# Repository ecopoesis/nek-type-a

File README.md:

# Natural Ergonomic Keyboard, Type A

One of the best keyboards ever made is the [Microsoft Natural Keyboard](https://en.wikipedia.org/wiki/Microsoft_Natural_Keyboard). 
Unfortunately modern versions of the natural keyboard are significantly worse then the original mid 90s versions. 
The goal of this project is to create a high-quality, open-source replacement for the natural keyboard.

## Goals

* Standard split-QWERTY layout mirroring the Microsoft Natural Keyboards
* No built-in number pad
* High quality mechanical switches
* Bluetooth or USB connection
* Plug and play (no-solder) microcontroller replacement
* Heirloom quality

## Design

The keyboard (and repo) is divided into the following parts:

* Body
* Electronics

### Body

The body has three major components: the aluminum unibody, the left and right steel switch plates and the acrylic access panel. 

Source files:
* `*.kbd.json` files are generated using the [keyboard_layout_editor.com](http://www.keyboard-layout-editor.com)
* `*.svg` and `*.dxf` files are built using [swillkb's Plate and Case Builder](http://builder.swillkb.com/) based on the `.kbd.json` files
  * The `*switch.*` files are the laser cutter templates
* `body.stl` and `body.step` are built from the [CadQuery](https://github.com/dcowden/cadquery) source file `body.py`. The easiest way to build this is to use the provided Docker image and `Makefile`:
  ```bash
    cd body && make
  ```    

You will need to have the following manufactured:
* Case
  * [`body.step`](body/target/body.step)
  * [screw tapping plan](drawings/bottom_view.pdf)
  * CNC from aluminum at [Xometry](http://xometry.com)
* Rubber gaskets
  * [`left_closed.dxf`](body/build_data/left_closed.dxf)
  * [`right_closed.dxf`](body/build_data/right_closed.dxf)
  * Laser cut from Buna-N Rubber 0.031 in at [Big Blue Saw](https://www.bigbluesaw.com/)
* Acrylic plate
  * [`plate.dxf`](drawings/plate.dxf)
  * Laser cut from Acrylic Plastic, Clear 0.118 in at [Big Blue Saw](https://www.bigbluesaw.com/)
* Steel plates
  * [`left_switch.dxf`](body/build_data/left_switch.dxf)
  * [`right_switch.dxf`](body/build_data/right_switch.dxf)
  * Laser cut from 304 Stainless Steel 1.5mm at [Lasergist](https://www.lasergist.com/)
  
You will need to buy:
* 8x M5x8mm screws
* 4x M5x20mm screws
* 3x M3 standoffs
* 3x M3x5mm screws
* 4x [M5 feet](https://www.amazon.com/gp/product/B000PWU9CC)
* 1x [USB-C panel mount](https://www.datapro.net/products/usb-c-panel-mount-extension-cable.html)
* 1x [19mm latching button](https://www.amazon.com/gp/product/B06XQZ3Y76)
* 1x [2-pin JST-XHP connector](https://www.amazon.com/gp/product/B0774TF39N)

### Electronics

The electronics are designed to be swappable. The left and right PCBs only contain the keyboard matrices and the ribbon connectors to the center PCB.

The PCBs can be made directly from the `BRD` files by [OSH Park](http://oshpark.com).

#### Left
[`left.brd`](eagle/nek-type-a/left.brd)

#### Right
[`right.brd`](eagle/nek-type-a/right.brd)

#### Center
[`center.brd`](eagle/nek-type-a/center.brd)

The center PCB uses a [MCP23017E-S/P](https://www.microchip.com/wwwproducts/en/MCP23017) I/O expander hooked to the microprocessor via the I2C bus.
The center is designed to use development boards that conform the [Adafruit](https://www.adafruit.com/feather) interface. 
The Feather is connected via headers on the center PCB so it can be swapped for models with different connectivity in the future was standards evolve.

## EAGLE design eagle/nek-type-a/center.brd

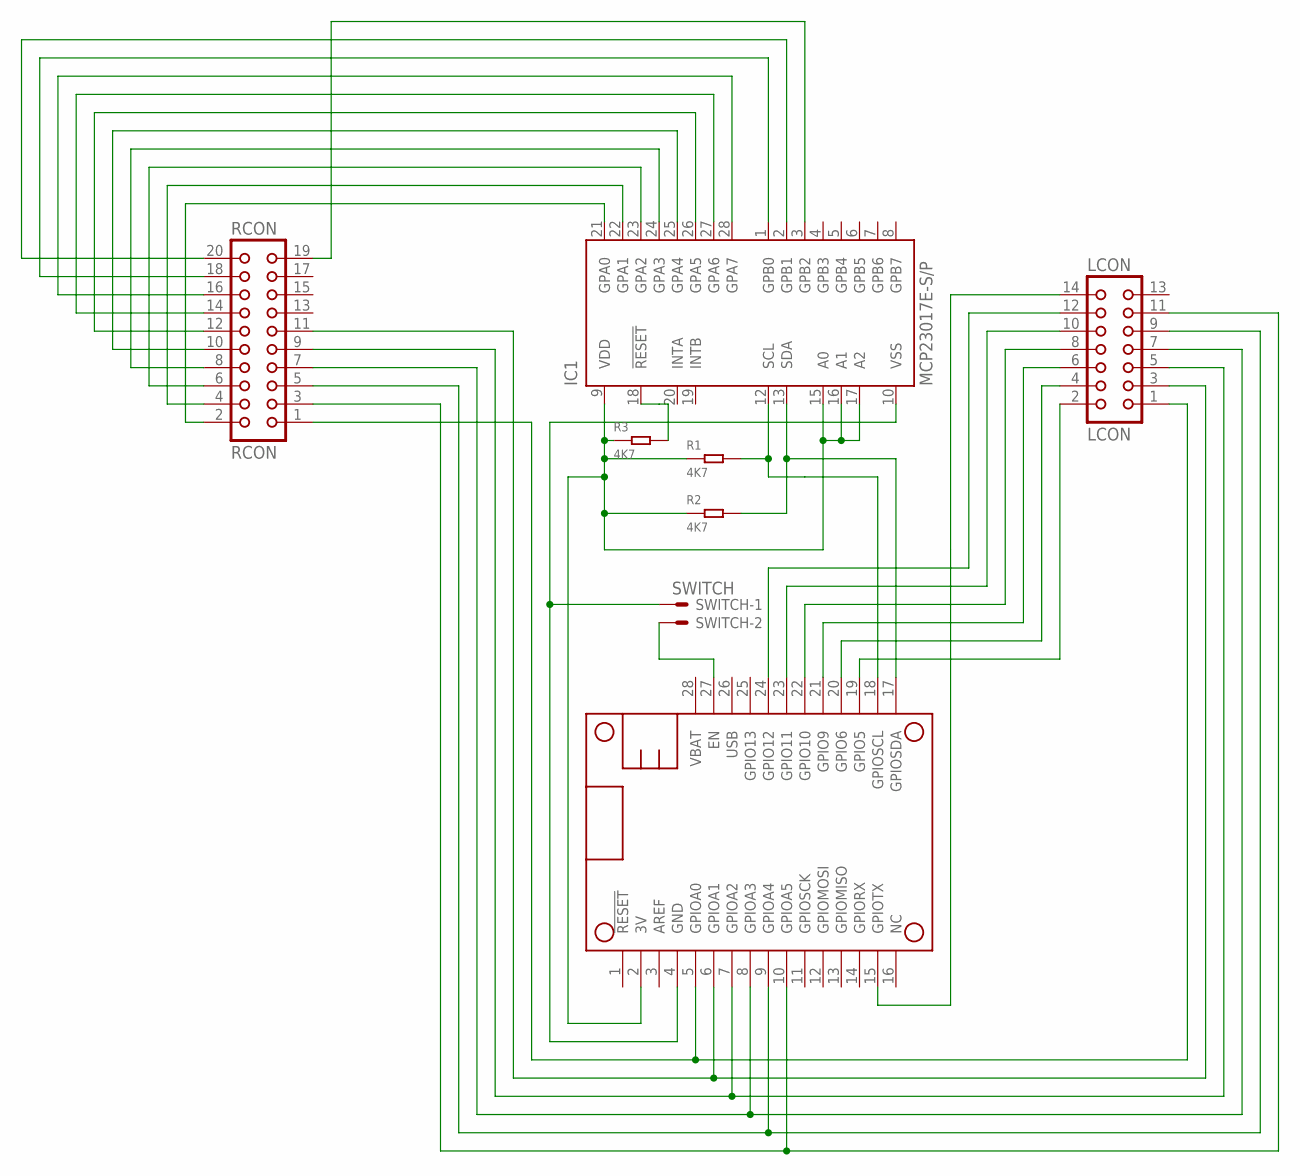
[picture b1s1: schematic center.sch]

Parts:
IC1: MCP23017E-S/P; DIL28-3
LCON: LCON; CON14
MS1: FEATHERWING_NODIM; FEATHERWING_DIM
R1, R2, R3: 4K7; PR-D2.3XL6.5MM
RCON: RCON; CON20
SWITCH: SWITCH; JST-XH-02-PACKAGE-LONG-PAD

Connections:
3V: IC1.9 (VDD), IC1.15 (A0), IC1.16 (A1), IC1.17 (A2), MS1.2 (3V), R1.1, R2.1, R3.1
EN: MS1.27 (EN), SWITCH.2
GND: IC1.10 (VSS), MS1.4 (GND), SWITCH.1
LCOL1: LCON.2, MS1.19 (GPIO5)
LCOL2: LCON.4, MS1.20 (GPIO6)
LCOL3: LCON.6, MS1.21 (GPIO9)
LCOL4: LCON.8, MS1.22 (GPIO10)
LCOL5: LCON.10, MS1.23 (GPIO11)
LCOL6: LCON.12, MS1.24 (GPIO12)
LCOL7: LCON.14, MS1.15 (GPIOTX)
RCOL1: IC1.21 (GPA0), RCON.2
RCOL2: IC1.22 (GPA1), RCON.4
RCOL3: IC1.23 (GPA2), RCON.6
RCOL4: IC1.24 (GPA3), RCON.8
RCOL5: IC1.25 (GPA4), RCON.10
RCOL6: IC1.26 (GPA5), RCON.12
RCOL7: IC1.27 (GPA6), RCON.14
RCOL8: IC1.28 (GPA7), RCON.16
RCOL9: IC1.1 (GPB0), RCON.18
RCOL10: IC1.2 (GPB1), RCON.20
RCOL11: IC1.3 (GPB2), RCON.19
RESET: IC1.18 (!RESET), R3.2
ROW1: LCON.1, MS1.5 (GPIOA0), RCON.1
ROW2: LCON.3, MS1.6 (GPIOA1), RCON.11
ROW3: LCON.5, MS1.7 (GPIOA2), RCON.9
ROW4: LCON.7, MS1.8 (GPIOA3), RCON.7
ROW5: LCON.9, MS1.9 (GPIOA4), RCON.5
ROW6: LCON.11, MS1.10 (GPIOA5), RCON.3
SCL: IC1.12 (SCL), MS1.18 (GPIOSCL), R1.2
SDA: IC1.13 (SDA), MS1.17 (GPIOSDA), R2.2

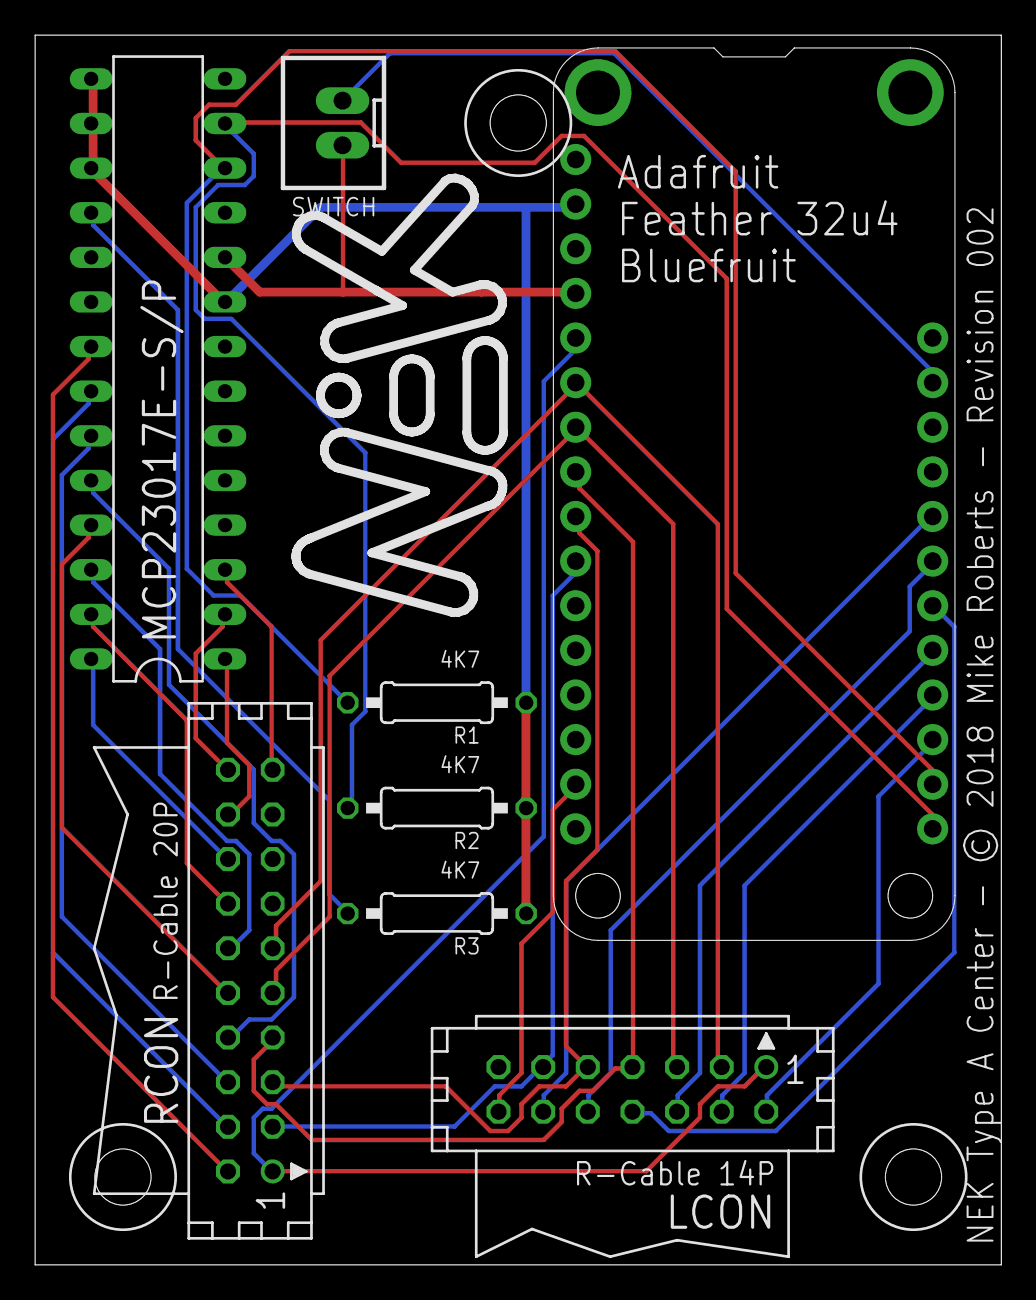
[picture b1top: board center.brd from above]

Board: 2 copper layers, 55.0 x 70.0 mm, 8 parts (0 on the bottom side), 30 nets.

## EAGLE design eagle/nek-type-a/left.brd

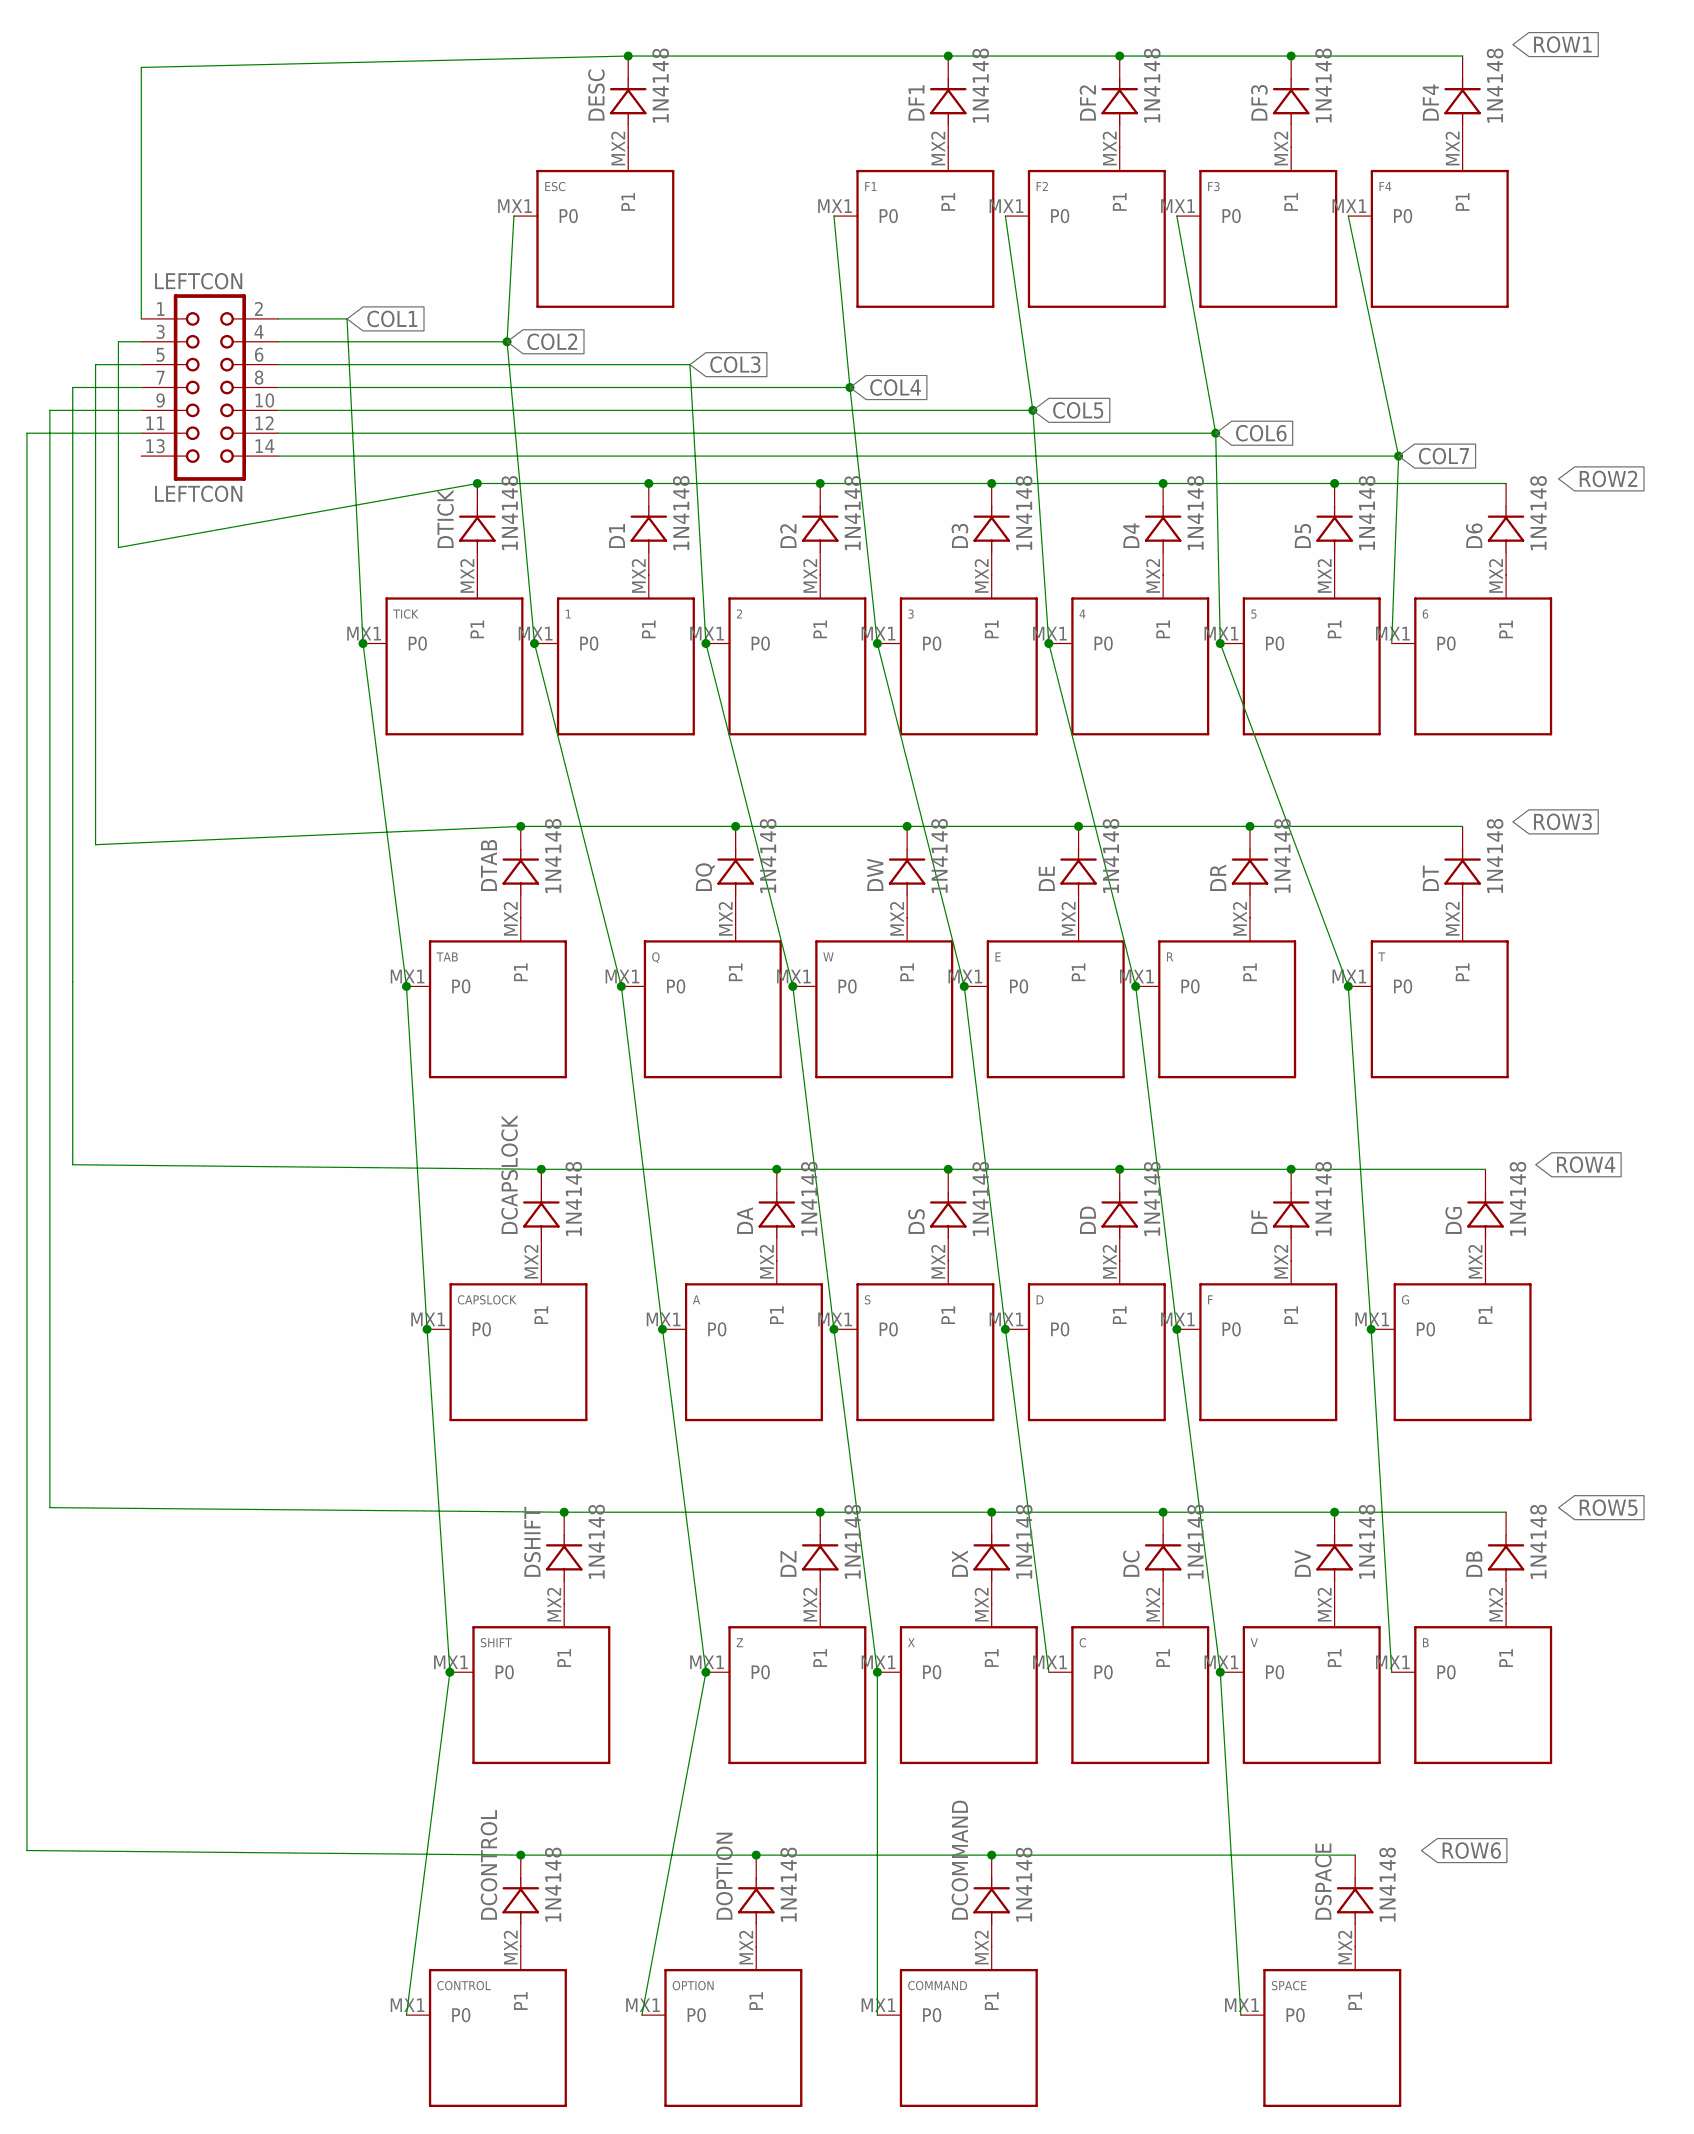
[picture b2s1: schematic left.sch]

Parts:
1, 2, 3, 4, 5, 6: KEYSWITCH-PLAIN-MX-1U; MX-1U
A: KEYSWITCH-PLAIN-MX-1U; MX-1U
B: KEYSWITCH-PLAIN-MX-1U; MX-1U
C: KEYSWITCH-PLAIN-MX-1U; MX-1U
CAPSLOCK: KEYSWITCH-PLAIN-MX-1U; MX-1U
COMMAND: KEYSWITCH-PLAIN-MX-1U; MX-1U
CONTROL: KEYSWITCH-PLAIN-MX-1U; MX-1U
D: KEYSWITCH-PLAIN-MX-1U; MX-1U
D1, D2, D3, D4, D5, D6: 1N4148; DO-35
DA: 1N4148; DO-35
DB: 1N4148; DO-35
DC: 1N4148; DO-35
DCAPSLOCK: 1N4148; DO-35
DCOMMAND: 1N4148; DO-35
DCONTROL: 1N4148; DO-35
DD: 1N4148; DO-35
DE: 1N4148; DO-35
DESC: 1N4148; DO-35
DF, DF1, DF2, DF3, DF4: 1N4148; DO-35
DG: 1N4148; DO-35
DOPTION: 1N4148; DO-35
DQ: 1N4148; DO-35
DR: 1N4148; DO-35
DS: 1N4148; DO-35
DSHIFT: 1N4148; DO-35
DSPACE: 1N4148; DO-35
DT: 1N4148; DO-35
DTAB: 1N4148; DO-35
DTICK: 1N4148; DO-35
DV: 1N4148; DO-35
DW: 1N4148; DO-35
DX: 1N4148; DO-35
DZ: 1N4148; DO-35
E: KEYSWITCH-PLAIN-MX-1U; MX-1U
ESC: KEYSWITCH-PLAIN-MX-1U; MX-1U
F, F1, F2, F3, F4: KEYSWITCH-PLAIN-MX-1U; MX-1U
G: KEYSWITCH-PLAIN-MX-1U; MX-1U
LEFTCON: LEFTCON; CON14
OPTION: KEYSWITCH-PLAIN-MX-1U; MX-1U
Q: KEYSWITCH-PLAIN-MX-1U; MX-1U
R: KEYSWITCH-PLAIN-MX-1U; MX-1U
S: KEYSWITCH-PLAIN-MX-1U; MX-1U
SHIFT: KEYSWITCH-PLAIN-MX-2U; MX-2U
SPACE: KEYSWITCH-PLAIN-MX-2U; MX-2U
T: KEYSWITCH-PLAIN-MX-1U; MX-1U
TAB: KEYSWITCH-PLAIN-MX-1U; MX-1U
TICK: KEYSWITCH-PLAIN-MX-1U; MX-1U
V: KEYSWITCH-PLAIN-MX-1U; MX-1U
W: KEYSWITCH-PLAIN-MX-1U; MX-1U
X: KEYSWITCH-PLAIN-MX-1U; MX-1U
Z: KEYSWITCH-PLAIN-MX-1U; MX-1U

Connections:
COL1: CAPSLOCK.MX1 (P0), CONTROL.MX1 (P0), LEFTCON.2, SHIFT.MX1 (P0), TAB.MX1 (P0), TICK.MX1 (P0)
COL2: 1.MX1 (P0), A.MX1 (P0), ESC.MX1 (P0), LEFTCON.4, OPTION.MX1 (P0), Q.MX1 (P0), Z.MX1 (P0)
COL3: 2.MX1 (P0), COMMAND.MX1 (P0), LEFTCON.6, S.MX1 (P0), W.MX1 (P0), X.MX1 (P0)
COL4: 3.MX1 (P0), C.MX1 (P0), D.MX1 (P0), E.MX1 (P0), F1.MX1 (P0), LEFTCON.8
COL5: 4.MX1 (P0), F.MX1 (P0), F2.MX1 (P0), LEFTCON.10, R.MX1 (P0), SPACE.MX1 (P0), V.MX1 (P0)
COL6: 5.MX1 (P0), B.MX1 (P0), F3.MX1 (P0), G.MX1 (P0), LEFTCON.12, T.MX1 (P0)
COL7: 6.MX1 (P0), F4.MX1 (P0), LEFTCON.14
unnamed: DESC.A, ESC.MX2 (P1)
unnamed: DF1.A, F1.MX2 (P1)
unnamed: DF2.A, F2.MX2 (P1)
unnamed: DF3.A, F3.MX2 (P1)
unnamed: DF4.A, F4.MX2 (P1)
unnamed: 6.MX2 (P1), D6.A
unnamed: 5.MX2 (P1), D5.A
unnamed: 4.MX2 (P1), D4.A
unnamed: 3.MX2 (P1), D3.A
unnamed: 2.MX2 (P1), D2.A
unnamed: 1.MX2 (P1), D1.A
unnamed: DTICK.A, TICK.MX2 (P1)
unnamed: DTAB.A, TAB.MX2 (P1)
unnamed: DQ.A, Q.MX2 (P1)
unnamed: DW.A, W.MX2 (P1)
unnamed: DE.A, E.MX2 (P1)
unnamed: DR.A, R.MX2 (P1)
unnamed: DT.A, T.MX2 (P1)
unnamed: CAPSLOCK.MX2 (P1), DCAPSLOCK.A
unnamed: A.MX2 (P1), DA.A
unnamed: DS.A, S.MX2 (P1)
unnamed: D.MX2 (P1), DD.A
unnamed: DF.A, F.MX2 (P1)
unnamed: DG.A, G.MX2 (P1)
unnamed: DSHIFT.A, SHIFT.MX2 (P1)
unnamed: DZ.A, Z.MX2 (P1)
unnamed: DX.A, X.MX2 (P1)
unnamed: C.MX2 (P1), DC.A
unnamed: DV.A, V.MX2 (P1)
unnamed: B.MX2 (P1), DB.A
unnamed: DSPACE.A, SPACE.MX2 (P1)
unnamed: COMMAND.MX2 (P1), DCOMMAND.A
unnamed: DOPTION.A, OPTION.MX2 (P1)
unnamed: CONTROL.MX2 (P1), DCONTROL.A
ROW1: DESC.C, DF1.C, DF2.C, DF3.C, DF4.C, LEFTCON.1
ROW2: D1.C, D2.C, D3.C, D4.C, D5.C, D6.C, DTICK.C, LEFTCON.3
ROW3: DE.C, DQ.C, DR.C, DT.C, DTAB.C, DW.C, LEFTCON.5
ROW4: DA.C, DCAPSLOCK.C, DD.C, DF.C, DG.C, DS.C, LEFTCON.7
ROW5: DB.C, DC.C, DSHIFT.C, DV.C, DX.C, DZ.C, LEFTCON.9
ROW6: DCOMMAND.C, DCONTROL.C, DOPTION.C, DSPACE.C, LEFTCON.11

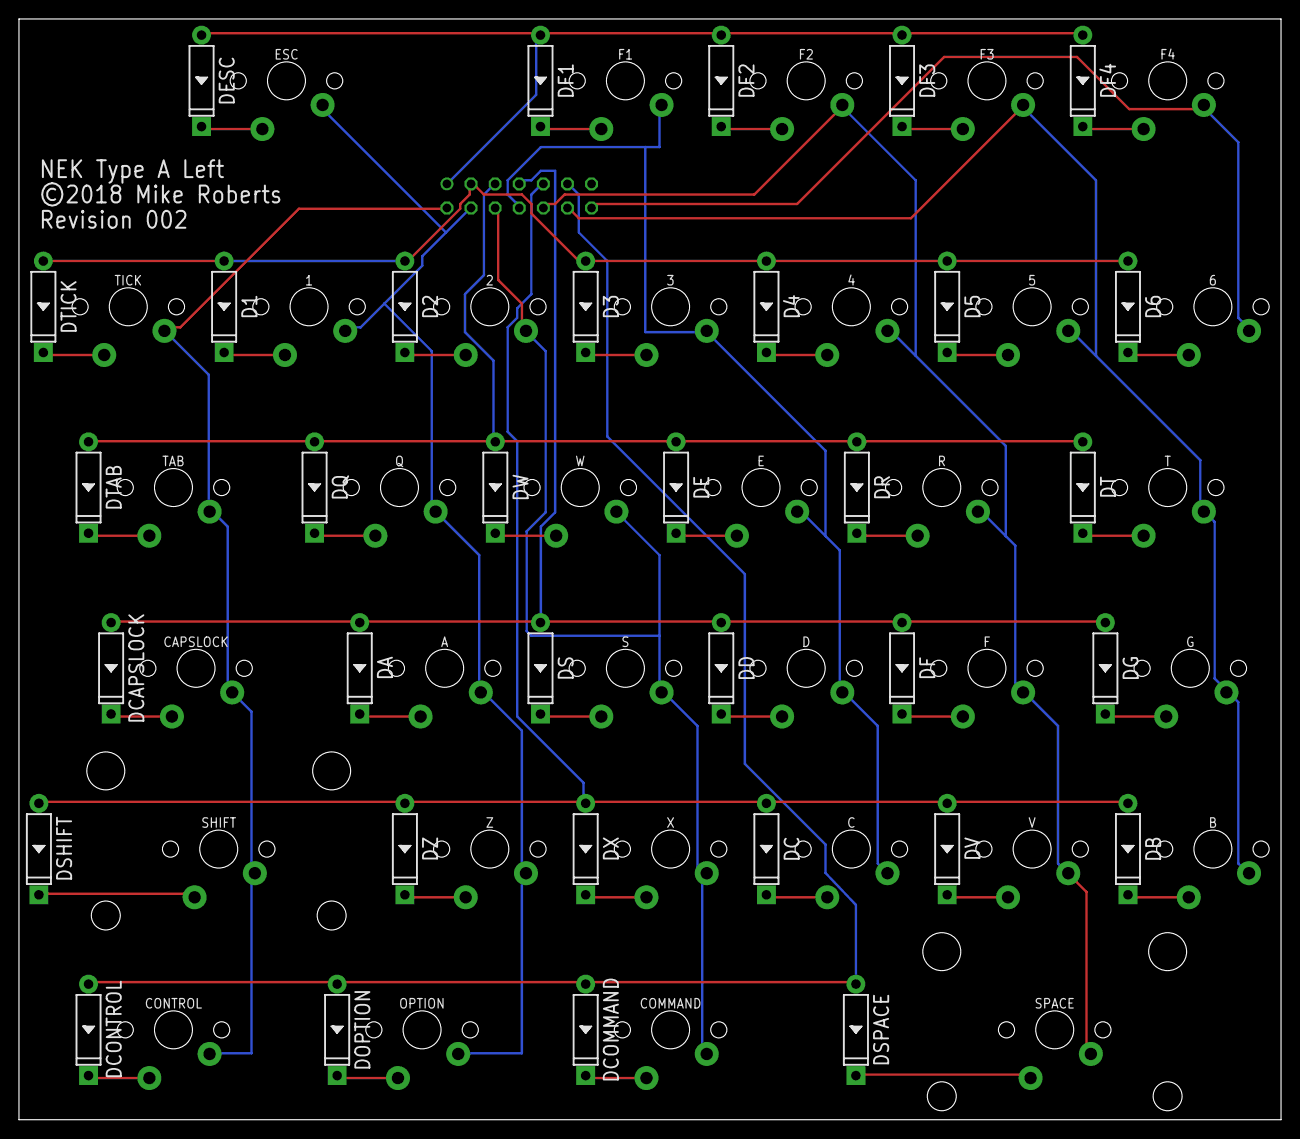
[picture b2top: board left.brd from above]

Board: 2 copper layers, 133.0 x 116.0 mm, 69 parts (1 on the bottom side), 47 nets.

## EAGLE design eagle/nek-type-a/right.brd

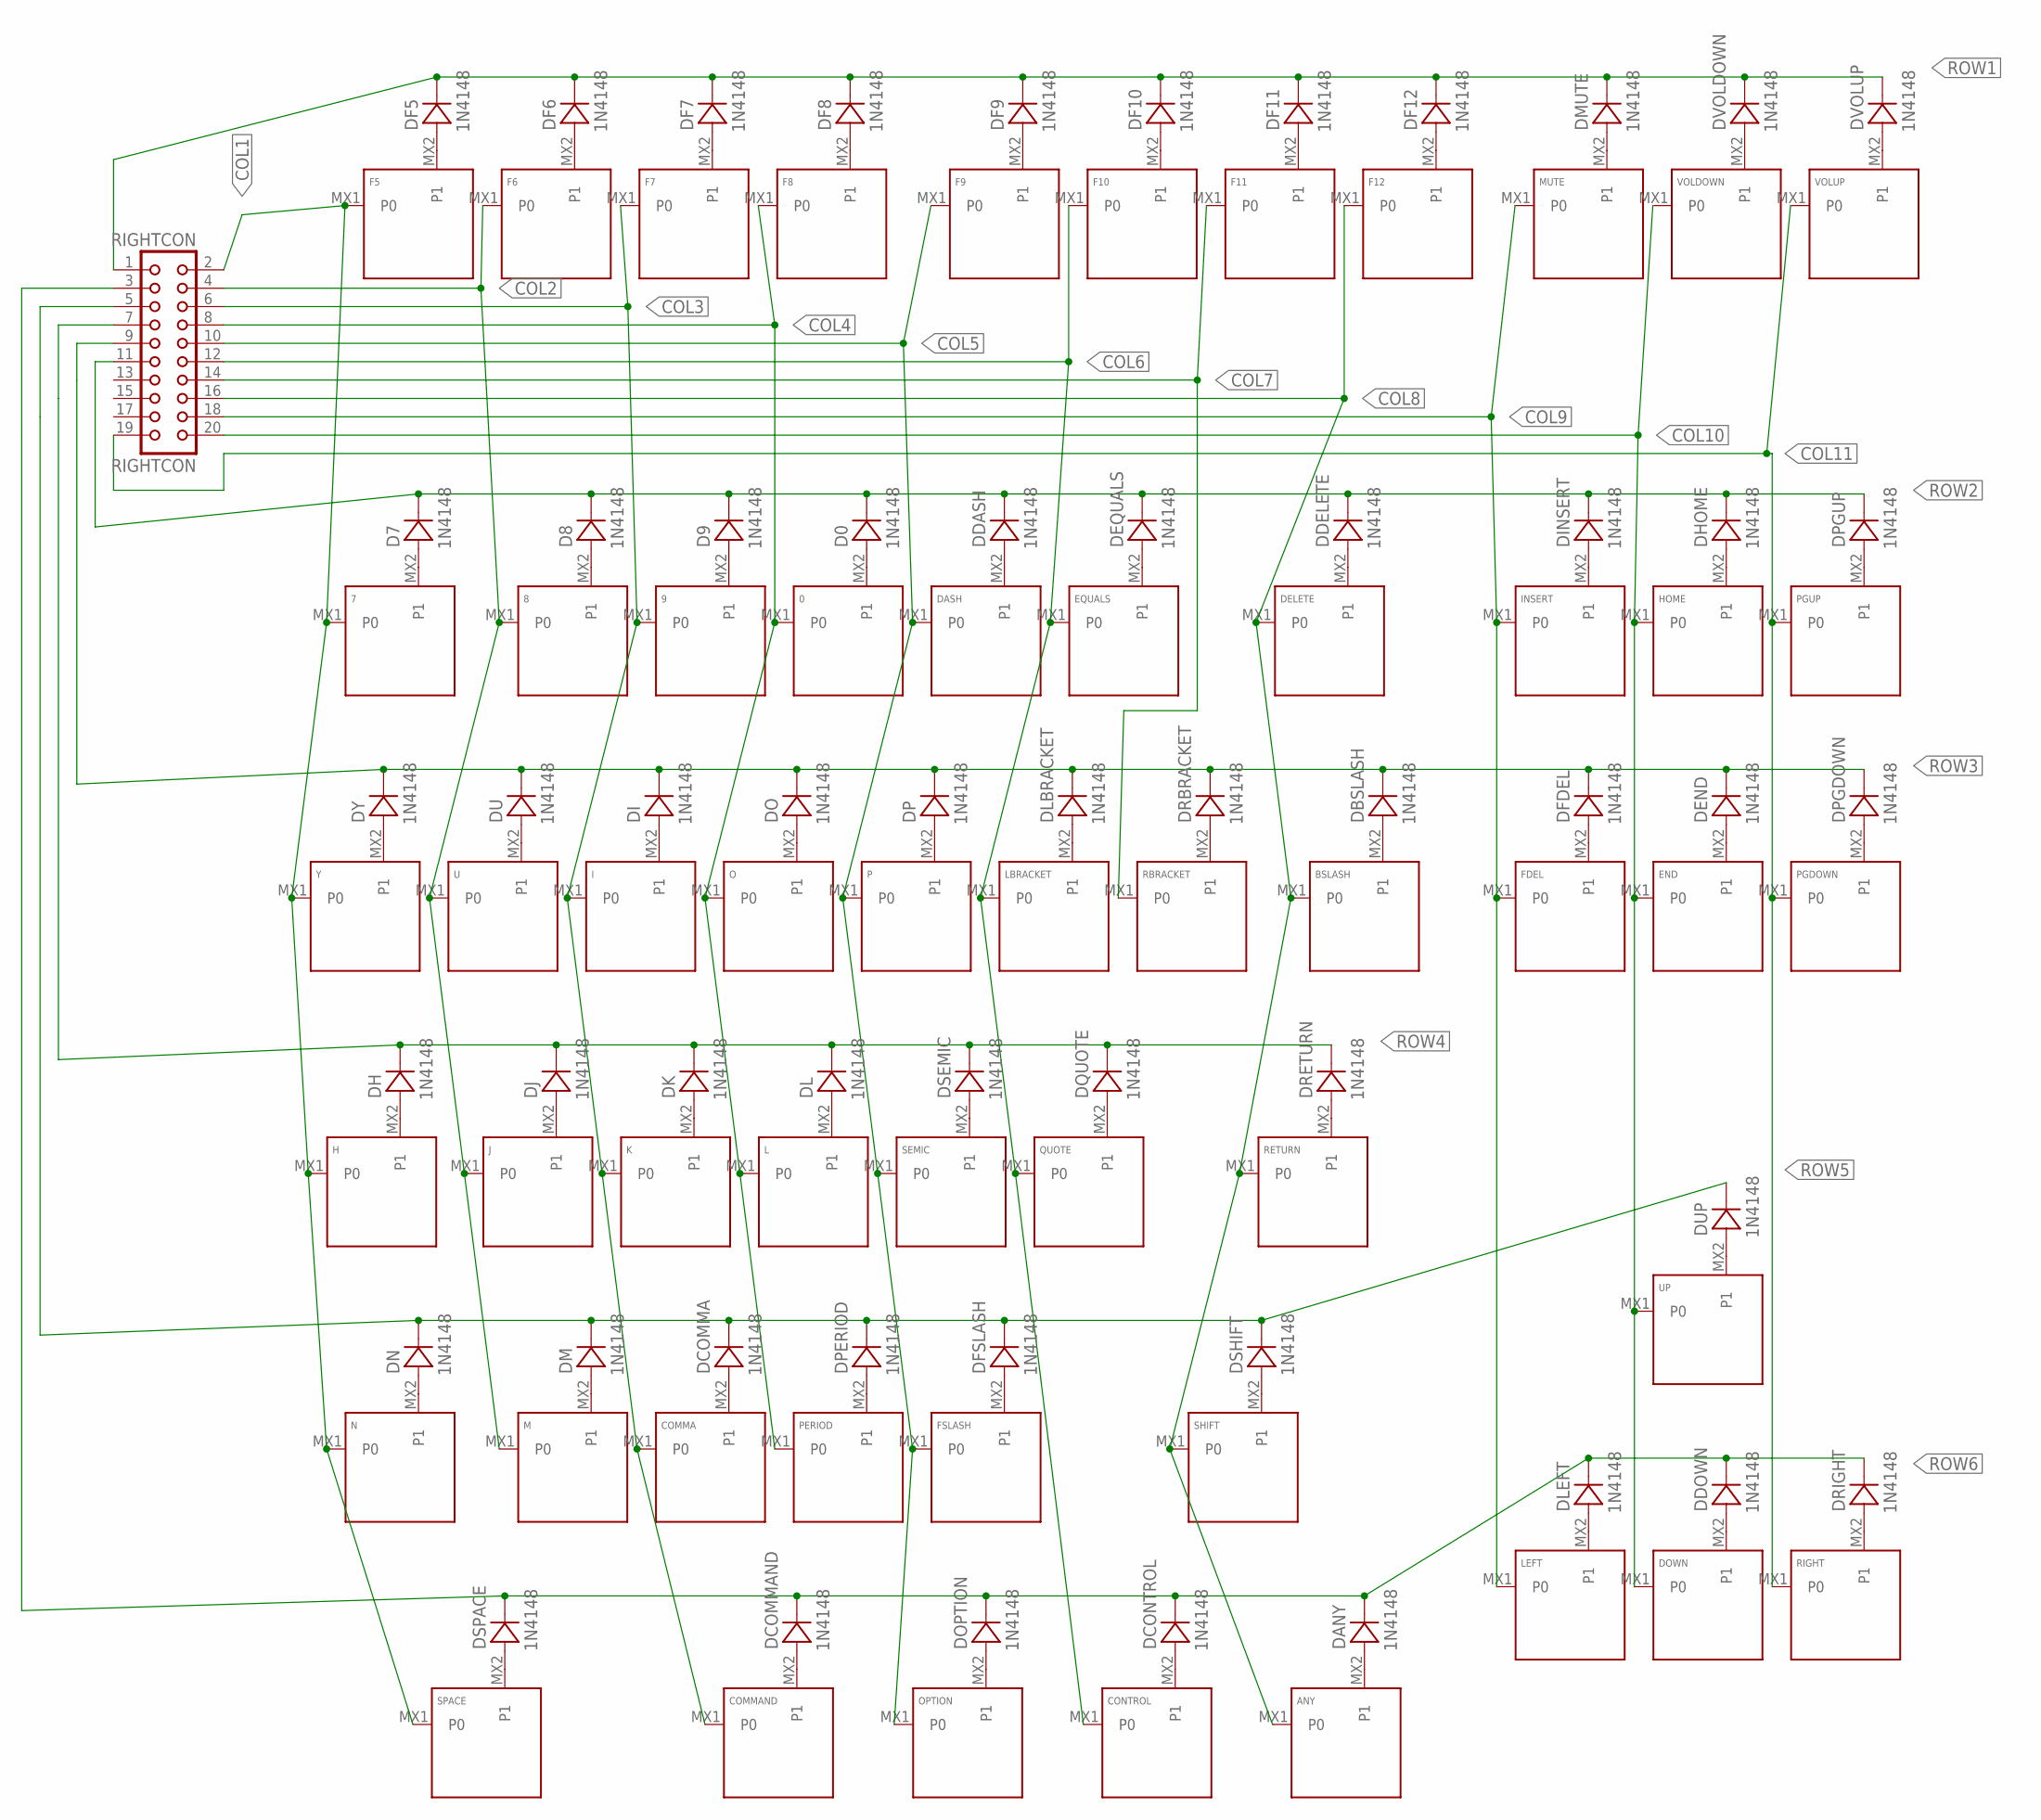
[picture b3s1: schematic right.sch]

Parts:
0, 7, 8, 9: KEYSWITCH-PLAIN-MX-1U; MX-1U
ANY: KEYSWITCH-PLAIN-MX-1U; MX-1U
BSLASH: KEYSWITCH-PLAIN-MX-1U; MX-1U
COMMA: KEYSWITCH-PLAIN-MX-1U; MX-1U
COMMAND: KEYSWITCH-PLAIN-MX-1U; MX-1U
CONTROL: KEYSWITCH-PLAIN-MX-1U; MX-1U
D0, D7, D8, D9: 1N4148; DO-35
DANY: 1N4148; DO-35
DASH: KEYSWITCH-PLAIN-MX-1U; MX-1U
DBSLASH: 1N4148; DO-35
DCOMMA: 1N4148; DO-35
DCOMMAND: 1N4148; DO-35
DCONTROL: 1N4148; DO-35
DDASH: 1N4148; DO-35
DDELETE: 1N4148; DO-35
DDOWN: 1N4148; DO-35
DELETE: KEYSWITCH-PLAIN-MX-2U; MX-2U
DEND: 1N4148; DO-35
DEQUALS: 1N4148; DO-35
DF5, DF6, DF7, DF8, DF9, DF10, DF11, DF12: 1N4148; DO-35
DFDEL: 1N4148; DO-35
DFSLASH: 1N4148; DO-35
DH: 1N4148; DO-35
DHOME: 1N4148; DO-35
DI: 1N4148; DO-35
DINSERT: 1N4148; DO-35
DJ: 1N4148; DO-35
DK: 1N4148; DO-35
DL: 1N4148; DO-35
DLBRACKET: 1N4148; DO-35
DLEFT: 1N4148; DO-35
DM: 1N4148; DO-35
DMUTE: 1N4148; DO-35
DN: 1N4148; DO-35
DO: 1N4148; DO-35
DOPTION: 1N4148; DO-35
DOWN: KEYSWITCH-PLAIN-MX-1U; MX-1U
DP: 1N4148; DO-35
DPERIOD: 1N4148; DO-35
DPGDOWN: 1N4148; DO-35
DPGUP: 1N4148; DO-35
DQUOTE: 1N4148; DO-35
DRBRACKET: 1N4148; DO-35
DRETURN: 1N4148; DO-35
DRIGHT: 1N4148; DO-35
DSEMIC: 1N4148; DO-35
DSHIFT: 1N4148; DO-35
DSPACE: 1N4148; DO-35
DU: 1N4148; DO-35
DUP: 1N4148; DO-35
DVOLDOWN: 1N4148; DO-35
DVOLUP: 1N4148; DO-35
DY: 1N4148; DO-35
END: KEYSWITCH-PLAIN-MX-1U; MX-1U
EQUALS: KEYSWITCH-PLAIN-MX-1U; MX-1U
F5, F6, F7, F8, F9, F10, F11, F12: KEYSWITCH-PLAIN-MX-1U; MX-1U
FDEL: KEYSWITCH-PLAIN-MX-1U; MX-1U
FSLASH: KEYSWITCH-PLAIN-MX-1U; MX-1U
H: KEYSWITCH-PLAIN-MX-1U; MX-1U
HOME: KEYSWITCH-PLAIN-MX-1U; MX-1U
I: KEYSWITCH-PLAIN-MX-1U; MX-1U
INSERT: KEYSWITCH-PLAIN-MX-1U; MX-1U
J: KEYSWITCH-PLAIN-MX-1U; MX-1U
K: KEYSWITCH-PLAIN-MX-1U; MX-1U
L: KEYSWITCH-PLAIN-MX-1U; MX-1U
LBRACKET: KEYSWITCH-PLAIN-MX-1U; MX-1U
LEFT: KEYSWITCH-PLAIN-MX-1U; MX-1U
M: KEYSWITCH-PLAIN-MX-1U; MX-1U
MUTE: KEYSWITCH-PLAIN-MX-1U; MX-1U
N: KEYSWITCH-PLAIN-MX-1U; MX-1U
O: KEYSWITCH-PLAIN-MX-1U; MX-1U
OPTION: KEYSWITCH-PLAIN-MX-1U; MX-1U
P: KEYSWITCH-PLAIN-MX-1U; MX-1U
PERIOD: KEYSWITCH-PLAIN-MX-1U; MX-1U
PGDOWN: KEYSWITCH-PLAIN-MX-1U; MX-1U
PGUP: KEYSWITCH-PLAIN-MX-1U; MX-1U
QUOTE: KEYSWITCH-PLAIN-MX-1U; MX-1U
RBRACKET: KEYSWITCH-PLAIN-MX-1U; MX-1U
RETURN: KEYSWITCH-PLAIN-MX-2U; MX-2U
RIGHT: KEYSWITCH-PLAIN-MX-1U; MX-1U
RIGHTCON: RIGHTCON; CON20
SEMIC: KEYSWITCH-PLAIN-MX-1U; MX-1U
SHIFT: KEYSWITCH-PLAIN-MX-2U; MX-2U
SPACE: KEYSWITCH-PLAIN-MX-2U; MX-2U
U: KEYSWITCH-PLAIN-MX-1U; MX-1U
UP: KEYSWITCH-PLAIN-MX-1U; MX-1U
VOLDOWN: KEYSWITCH-PLAIN-MX-1U; MX-1U
VOLUP: KEYSWITCH-PLAIN-MX-1U; MX-1U
Y: KEYSWITCH-PLAIN-MX-1U; MX-1U

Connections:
COL1: 7.MX1 (P0), F5.MX1 (P0), H.MX1 (P0), N.MX1 (P0), RIGHTCON.2, SPACE.MX1 (P0), Y.MX1 (P0)
COL2: 8.MX1 (P0), F6.MX1 (P0), J.MX1 (P0), M.MX1 (P0), RIGHTCON.4, U.MX1 (P0)
COL3: 9.MX1 (P0), COMMA.MX1 (P0), COMMAND.MX1 (P0), F7.MX1 (P0), I.MX1 (P0), K.MX1 (P0), RIGHTCON.6
COL4: 0.MX1 (P0), F8.MX1 (P0), L.MX1 (P0), O.MX1 (P0), PERIOD.MX1 (P0), RIGHTCON.8
COL5: DASH.MX1 (P0), F9.MX1 (P0), FSLASH.MX1 (P0), OPTION.MX1 (P0), P.MX1 (P0), RIGHTCON.10, SEMIC.MX1 (P0)
COL6: CONTROL.MX1 (P0), EQUALS.MX1 (P0), F10.MX1 (P0), LBRACKET.MX1 (P0), QUOTE.MX1 (P0), RIGHTCON.12
COL7: F11.MX1 (P0), RBRACKET.MX1 (P0), RIGHTCON.14
COL8: ANY.MX1 (P0), BSLASH.MX1 (P0), DELETE.MX1 (P0), F12.MX1 (P0), RETURN.MX1 (P0), RIGHTCON.16, SHIFT.MX1 (P0)
COL9: FDEL.MX1 (P0), INSERT.MX1 (P0), LEFT.MX1 (P0), MUTE.MX1 (P0), RIGHTCON.18
COL10: DOWN.MX1 (P0), END.MX1 (P0), HOME.MX1 (P0), RIGHTCON.20, UP.MX1 (P0), VOLDOWN.MX1 (P0)
COL11: PGDOWN.MX1 (P0), PGUP.MX1 (P0), RIGHT.MX1 (P0), RIGHTCON.19, VOLUP.MX1 (P0)
unnamed: DF5.A, F5.MX2 (P1)
unnamed: DF6.A, F6.MX2 (P1)
unnamed: DF7.A, F7.MX2 (P1)
unnamed: DF8.A, F8.MX2 (P1)
unnamed: DF9.A, F9.MX2 (P1)
unnamed: DF10.A, F10.MX2 (P1)
unnamed: DF11.A, F11.MX2 (P1)
unnamed: DF12.A, F12.MX2 (P1)
unnamed: DMUTE.A, MUTE.MX2 (P1)
unnamed: DVOLDOWN.A, VOLDOWN.MX2 (P1)
unnamed: DVOLUP.A, VOLUP.MX2 (P1)
unnamed: 7.MX2 (P1), D7.A
unnamed: 8.MX2 (P1), D8.A
unnamed: 9.MX2 (P1), D9.A
unnamed: 0.MX2 (P1), D0.A
unnamed: DASH.MX2 (P1), DDASH.A
unnamed: DEQUALS.A, EQUALS.MX2 (P1)
unnamed: DDELETE.A, DELETE.MX2 (P1)
unnamed: DINSERT.A, INSERT.MX2 (P1)
unnamed: DHOME.A, HOME.MX2 (P1)
unnamed: DPGUP.A, PGUP.MX2 (P1)
unnamed: DY.A, Y.MX2 (P1)
unnamed: DU.A, U.MX2 (P1)
unnamed: DI.A, I.MX2 (P1)
unnamed: DO.A, O.MX2 (P1)
unnamed: DP.A, P.MX2 (P1)
unnamed: DLBRACKET.A, LBRACKET.MX2 (P1)
unnamed: DRBRACKET.A, RBRACKET.MX2 (P1)
unnamed: BSLASH.MX2 (P1), DBSLASH.A
unnamed: DFDEL.A, FDEL.MX2 (P1)
unnamed: DEND.A, END.MX2 (P1)
unnamed: DPGDOWN.A, PGDOWN.MX2 (P1)
unnamed: DH.A, H.MX2 (P1)
unnamed: DJ.A, J.MX2 (P1)
unnamed: DK.A, K.MX2 (P1)
unnamed: DL.A, L.MX2 (P1)
unnamed: DSEMIC.A, SEMIC.MX2 (P1)
unnamed: DQUOTE.A, QUOTE.MX2 (P1)
unnamed: DRETURN.A, RETURN.MX2 (P1)
unnamed: DN.A, N.MX2 (P1)
unnamed: DM.A, M.MX2 (P1)
unnamed: COMMA.MX2 (P1), DCOMMA.A
unnamed: DPERIOD.A, PERIOD.MX2 (P1)
unnamed: DFSLASH.A, FSLASH.MX2 (P1)
unnamed: DSHIFT.A, SHIFT.MX2 (P1)
unnamed: DSPACE.A, SPACE.MX2 (P1)
unnamed: COMMAND.MX2 (P1), DCOMMAND.A
unnamed: DOPTION.A, OPTION.MX2 (P1)
unnamed: CONTROL.MX2 (P1), DCONTROL.A
unnamed: ANY.MX2 (P1), DANY.A
unnamed: DLEFT.A, LEFT.MX2 (P1)
unnamed: DDOWN.A, DOWN.MX2 (P1)
unnamed: DRIGHT.A, RIGHT.MX2 (P1)
unnamed: DUP.A, UP.MX2 (P1)
ROW1: DF5.C, DF6.C, DF7.C, DF8.C, DF9.C, DF10.C, DF11.C, DF12.C, DMUTE.C, DVOLDOWN.C, DVOLUP.C, RIGHTCON.1
ROW2: D0.C, D7.C, D8.C, D9.C, DDASH.C, DDELETE.C, DEQUALS.C, DHOME.C, DINSERT.C, DPGUP.C, RIGHTCON.11
ROW3: DBSLASH.C, DEND.C, DFDEL.C, DI.C, DLBRACKET.C, DO.C, DP.C, DPGDOWN.C, DRBRACKET.C, DU.C, DY.C, RIGHTCON.9
ROW4: DH.C, DJ.C, DK.C, DL.C, DQUOTE.C, DRETURN.C, DSEMIC.C, RIGHTCON.7
ROW5: DCOMMA.C, DFSLASH.C, DM.C, DN.C, DPERIOD.C, DSHIFT.C, DUP.C, RIGHTCON.5
ROW6: DANY.C, DCOMMAND.C, DCONTROL.C, DDOWN.C, DLEFT.C, DOPTION.C, DRIGHT.C, DSPACE.C, RIGHTCON.3

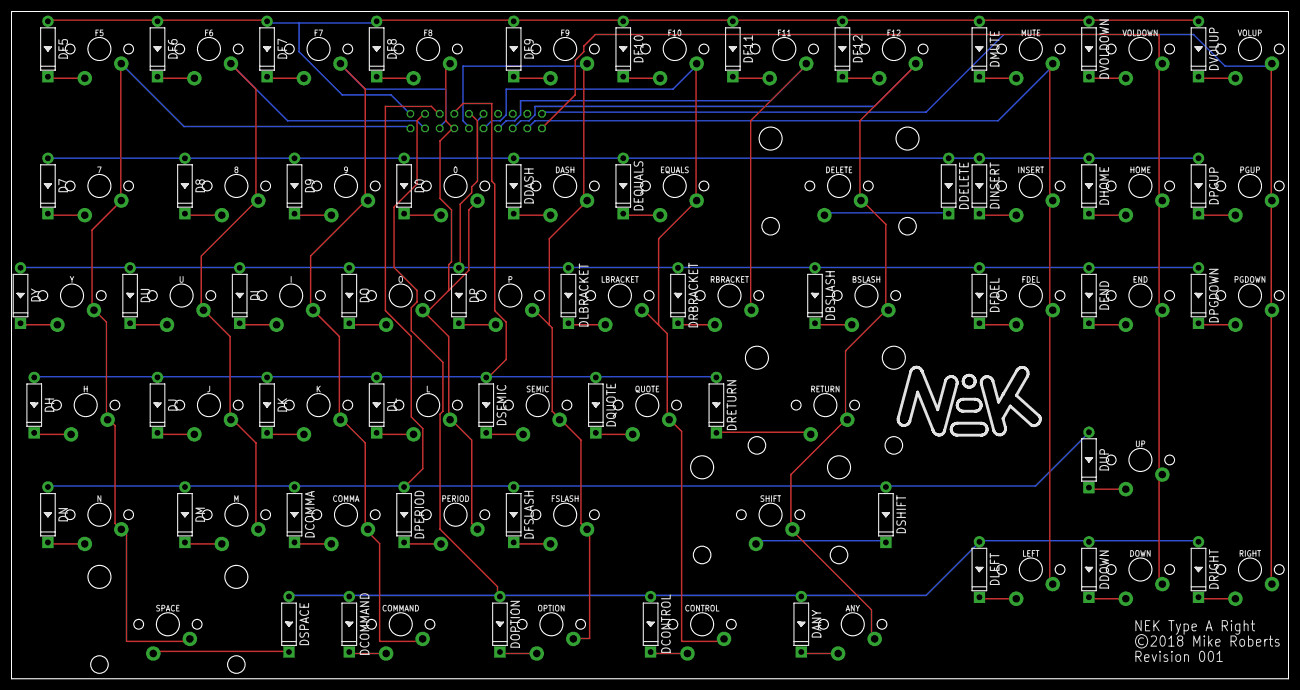
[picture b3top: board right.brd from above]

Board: 2 copper layers, 222.0 x 116.0 mm, 109 parts (1 on the bottom side), 71 nets.

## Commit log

2018-04-20 basic body
2018-04-20 high left
2018-04-20 split
2018-04-25 switch to bosl, quaternions are awesome
2018-04-25 add slope
2018-04-26 filletted edges
2018-04-28 completish body
2018-04-29 right well start
2018-04-29 complete right well
2018-04-29 left well
2018-04-29 better corners
2018-04-29 decrease well size
2018-04-29 right wrist rest
2018-04-29 left wrist
2018-04-29 pivot coord
2018-04-29 gap_x and gap_z
2018-04-29 finally, center polygon
2018-04-30 fix center poly
2018-04-30 right edge fillet
2018-04-30 fix center manifold
2018-04-30 top right fillet
2018-05-02 bottom right
2018-05-02 left edge
2018-05-02 left top and bottom
2018-05-02 left front corner
2018-05-02 better placement
2018-05-03 compute true split angle correctly
2018-05-03 back left corner
2018-05-03 right corners
2018-05-13 remove fillets
2018-05-13 better left fillets
2018-05-13 better right fillet
2018-05-13 hull all the things
2018-05-13 readd the wells
2018-05-13 new key layouts
2018-05-13 adjust y to get under 12"
2018-05-27 initial cadquery version
2018-05-28 angles
2018-05-28 both sides
2018-05-28 move right to 0,0,0
2018-05-28 left to 0,0,0
2018-05-29 unfilleted center
2018-05-29 add fillets back
2018-06-14 make
2018-06-15 fix spacing, docker
2018-06-15 everything in python works and make!
2018-06-17 mastery over planes
2018-06-17 back with broken fillets
2018-06-18 add readme
2018-06-18 svgtools
2018-06-18 add stl
2018-06-18 move body to subdir
2018-06-18 remove bosl
2018-06-26 basic svg import and extruding
2018-06-29 right top plate
2018-06-29 left top plate
2018-06-29 refactor python libs
2018-06-29 fix right kbd error
2018-06-30 hollow bottoms
2018-06-30 readd back, fix cut throughs
2018-07-02 fillet top late cutouts
2018-07-02 smooth bottom
2018-07-05 refactor, todo
2018-07-06 remove rounded back corners
2018-07-10 usb cutout, no screw hole
2018-07-11 refactor out coordplane
2018-07-11 more refactoring
2018-08-19 left schematic
2018-08-19 columns
2018-08-19 rows connected
2018-08-19 initial left board
2018-08-19 eagle gitignore
2018-08-19 left routed
2018-08-19 completed left pcb
2018-08-28 logo
2018-08-30 better logo, right pcb
2018-09-04 move diodes away from stabilizers
2018-10-08 fix body errors
2018-10-08 center board
2018-10-08 center rev 001
2018-10-14 spine
2018-10-27 keykaps needed
2018-10-27 cavity fillet
2018-10-27 encheapen
2018-10-27 pcb mount
2018-10-27 plate mounting holes
2018-10-27 power button
2018-10-27 bottom plate position
2018-10-27 bottom plate
2018-10-28 feet!
2018-10-28 fillets!
2018-10-28 larger plates
2018-10-28 adjust fit
2018-10-28 export plate, make nonsense
2018-10-28 update for washers
2018-10-28 cleanup, files for lasercutting, resolution
2018-10-28 solid
2018-10-29 convert points to arcs
2018-10-30 fix inner corners
2018-10-30 wider?
2018-10-31 reangle
2018-10-31 compute back plane height
2018-11-03 step down pockets
2018-11-06 fixes and hopefully final
2018-12-21 center rev 2
2019-01-20 foam
2019-02-18 drawings
2019-02-18 better?
2019-02-18 images
2019-02-18 improve readme
2022-03-25 list non-1u key sizes
2022-03-25 bolder

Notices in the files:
eagle/nek-type-a/center.brd:
NEK Type A Center - © 2018 Mike Roberts - Revision 002
